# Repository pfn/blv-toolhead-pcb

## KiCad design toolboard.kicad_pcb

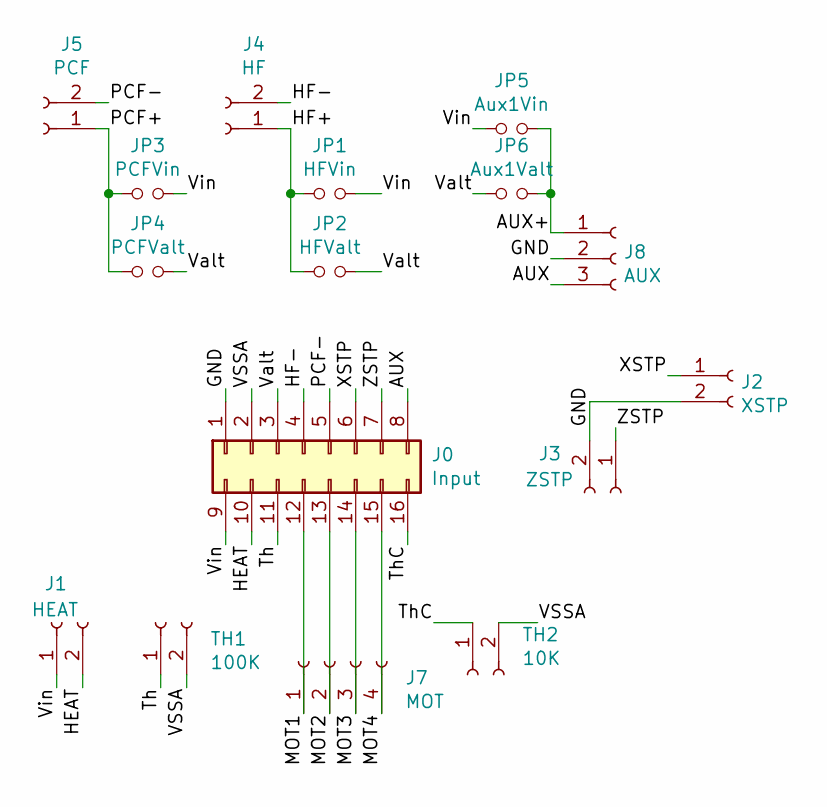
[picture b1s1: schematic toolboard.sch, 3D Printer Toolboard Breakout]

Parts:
J0: Input; Molex_Micro-Fit_3.0_43045-1600_2x08_P3.00mm_Horizontal
J1: HEAT; Molex_Micro-Fit_3.0_43650-0215_1x02_P3.00mm_Vertical
J2: XSTP; JST_XH_B2B-XH-A_1x02_P2.50mm_Vertical
J3: ZSTP; JST_XH_B2B-XH-A_1x02_P2.50mm_Vertical
J4: HF; JST_XH_B2B-XH-A_1x02_P2.50mm_Vertical
J5: PCF; JST_XH_B2B-XH-A_1x02_P2.50mm_Vertical
J7: MOT; JST_XH_B4B-XH-A_1x04_P2.50mm_Vertical
J8: AUX; JST_XH_B3B-XH-A_1x03_P2.50mm_Vertical
JP1: HFVin; SolderJumper-2_P1.3mm_Open_TrianglePad1.0x1.5mm
JP2: HFValt; SolderJumper-2_P1.3mm_Open_TrianglePad1.0x1.5mm
JP3: PCFVin; SolderJumper-2_P1.3mm_Open_TrianglePad1.0x1.5mm
JP4: PCFValt; SolderJumper-2_P1.3mm_Open_TrianglePad1.0x1.5mm
JP5: Aux1Vin; SolderJumper-2_P1.3mm_Open_TrianglePad1.0x1.5mm
JP6: Aux1Valt; SolderJumper-2_P1.3mm_Open_TrianglePad1.0x1.5mm
TH1: 100K; JST_XH_B2B-XH-A_1x02_P2.50mm_Vertical
TH2: 10K; JST_XH_B2B-XH-A_1x02_P2.50mm_Vertical

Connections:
/AUX: J0.8, J8.3
/AUX+: J8.1, JP5.1, JP6.1
/GND: J0.1, J2.2, J3.2, J8.2
/HEAT: J0.10, J1.2
/HF+: J4.1, JP1.1, JP2.1
/HF-: J0.4, J4.2
/MOT1: J0.12, J7.1
/MOT2: J0.13, J7.2
/MOT3: J0.14, J7.3
/MOT4: J0.15, J7.4
/PCF+: J5.1, JP3.1, JP4.1
/PCF-: J0.5, J5.2
/Th: J0.11, TH1.1
/ThC: J0.16, TH2.1
/VSSA: J0.2, TH1.2, TH2.2
/Valt: J0.3, JP2.2, JP4.2, JP6.2
/Vin: J0.9, J1.1, JP1.2, JP3.2, JP5.2
/XSTP: J0.6, J2.1
/ZSTP: J0.7, J3.1

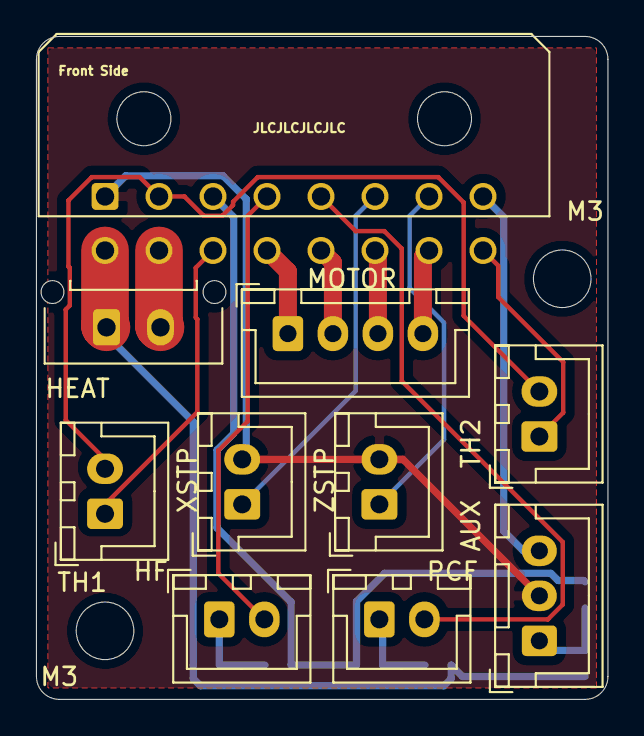
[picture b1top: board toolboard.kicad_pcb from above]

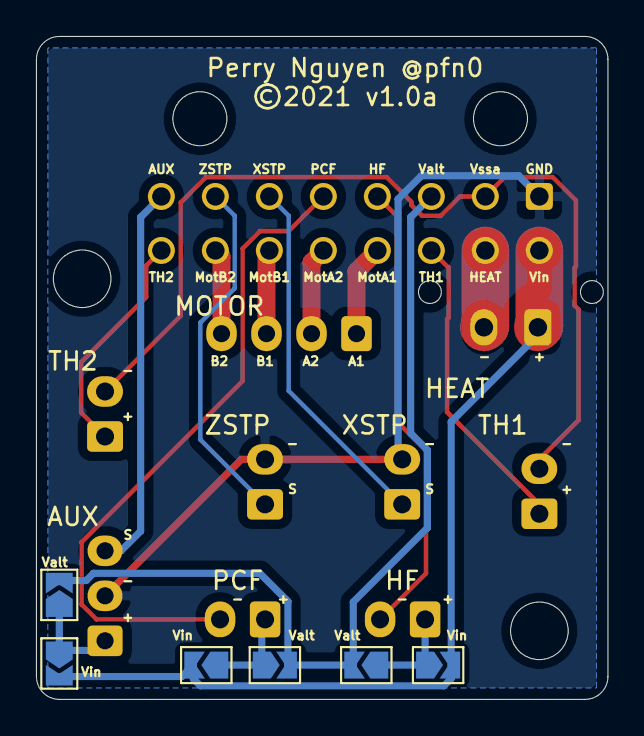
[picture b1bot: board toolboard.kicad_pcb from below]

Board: 2 copper layers, 31.8 x 36.8 mm, 18 parts (6 on the bottom side), 19 nets.

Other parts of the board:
M3, M3#2: M3; MountingHole_3.2mm_M3_ISO14580

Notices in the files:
toolboard.kicad_pcb:
©2021 v1.0a
